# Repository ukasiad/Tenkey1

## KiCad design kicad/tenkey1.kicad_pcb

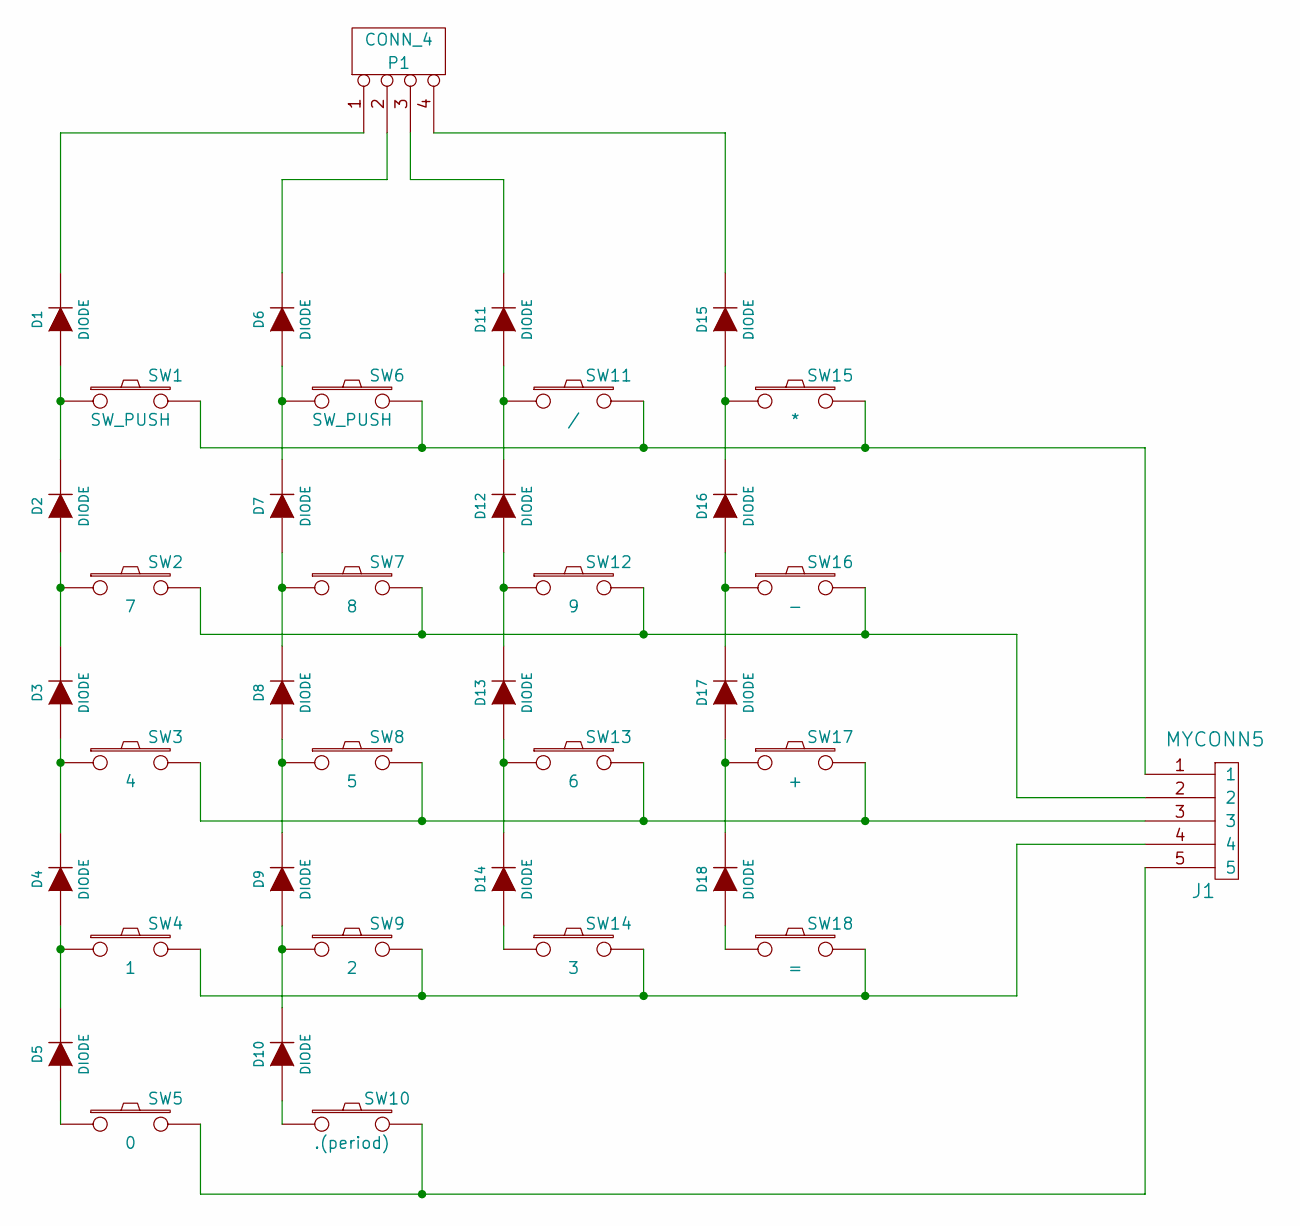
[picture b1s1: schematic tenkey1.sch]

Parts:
D1, D2, D3, D4, D5, D6, D7, D8, D9, D10, D11, D12, D13, D14, D15, D16, D17, D18: DIODE
J1: MYCONN5
P1: CONN_4
SW1, SW6: SW_PUSH
SW2: 7
SW3: 4
SW4: 1
SW5: 0
SW7: 8
SW8: 5
SW9: 2
SW10: .(period)
SW11: /
SW12: 9
SW13: 6
SW14: 3
SW15: *
SW16: -
SW17: +
SW18: =

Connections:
unnamed: D5.1 (A), SW5.1
unnamed: D10.1 (A), SW10.1
unnamed: D1.2 (K), P1.1
unnamed: D14.1 (A), SW14.1
unnamed: D18.1 (A), SW18.1
unnamed: D6.2 (K), P1.2
unnamed: D11.2 (K), P1.3
unnamed: D15.2 (K), P1.4
unnamed: J1.2, SW2.2, SW7.2, SW12.2, SW16.2
unnamed: D13.1 (A), D14.2 (K), SW13.1
unnamed: J1.5, SW5.2, SW10.2
unnamed: D15.1 (A), D16.2 (K), SW15.1
unnamed: D16.1 (A), D17.2 (K), SW16.1
unnamed: D12.1 (A), D13.2 (K), SW12.1
unnamed: D17.1 (A), D18.2 (K), SW17.1
unnamed: J1.3, SW3.2, SW8.2, SW13.2, SW17.2
unnamed: J1.1, SW1.2, SW6.2, SW11.2, SW15.2
unnamed: D6.1 (A), D7.2 (K), SW6.1
unnamed: D2.1 (A), D3.2 (K), SW2.1
unnamed: D3.1 (A), D4.2 (K), SW3.1
unnamed: D4.1 (A), D5.2 (K), SW4.1
unnamed: D7.1 (A), D8.2 (K), SW7.1
unnamed: D8.1 (A), D9.2 (K), SW8.1
unnamed: D9.1 (A), D10.2 (K), SW9.1
unnamed: D11.1 (A), D12.2 (K), SW11.1
unnamed: J1.4, SW4.2, SW9.2, SW14.2, SW18.2
unnamed: D1.1 (A), D2.2 (K), SW1.1

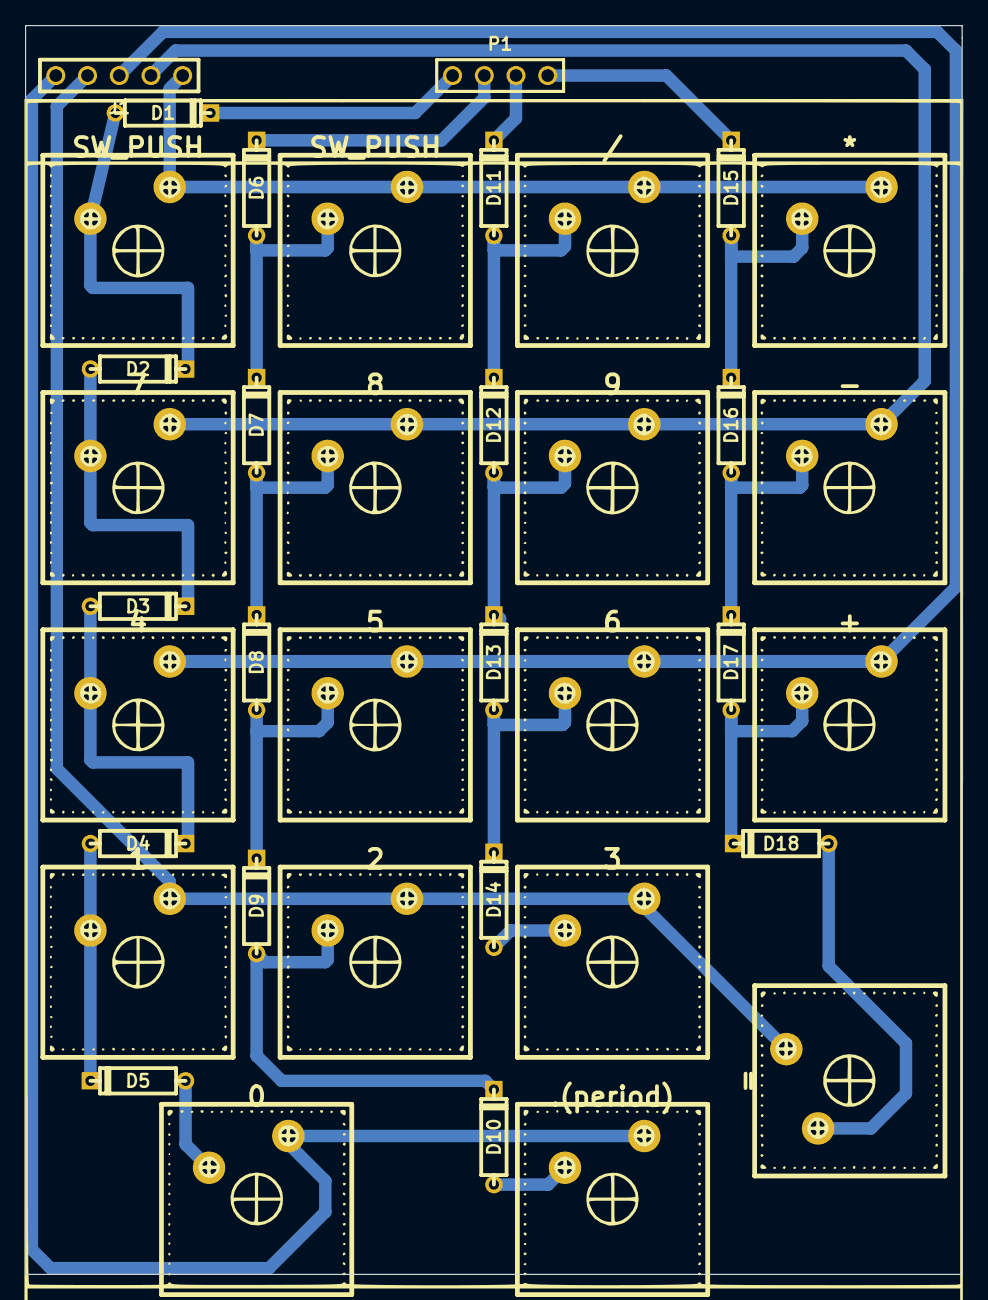
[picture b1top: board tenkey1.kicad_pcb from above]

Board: 2 copper layers, 75.0 x 100.0 mm, 38 parts (0 on the bottom side), 27 nets.

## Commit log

2014-04-27 テンキー1資料
